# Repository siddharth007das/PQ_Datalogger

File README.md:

# PQ_Datalogger
This work presents a high-precision, edge-computing data logger for real-time spike-based load profiling. The system integrates Halleffect current sensors, high-voltage transducers, and high-speed ADCs controlled by an STM32H7 microcontroller to perform synchronised voltage–current sampling, PQ computation, and transient detection.

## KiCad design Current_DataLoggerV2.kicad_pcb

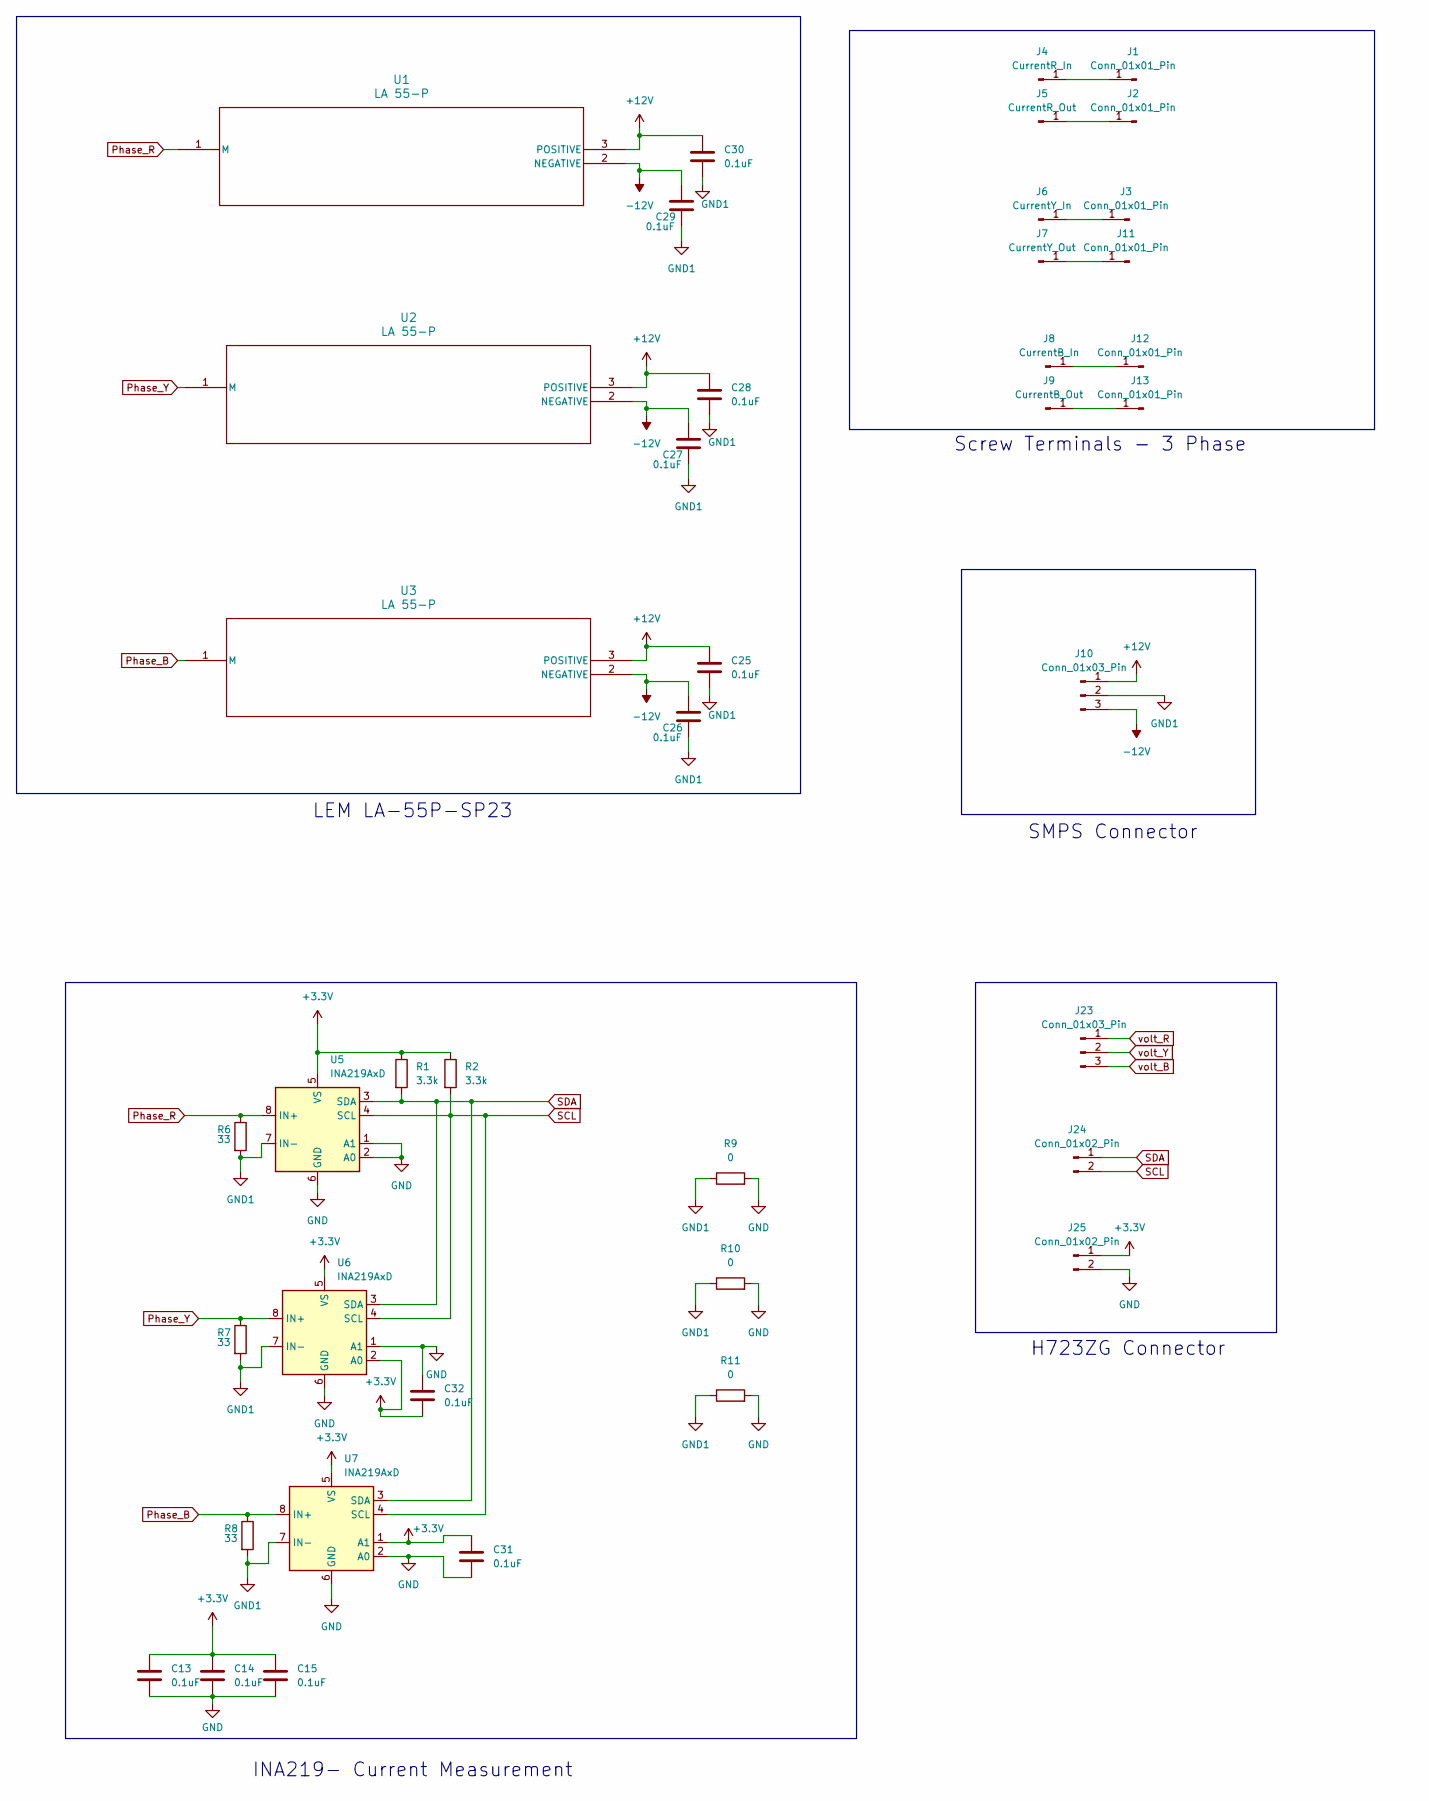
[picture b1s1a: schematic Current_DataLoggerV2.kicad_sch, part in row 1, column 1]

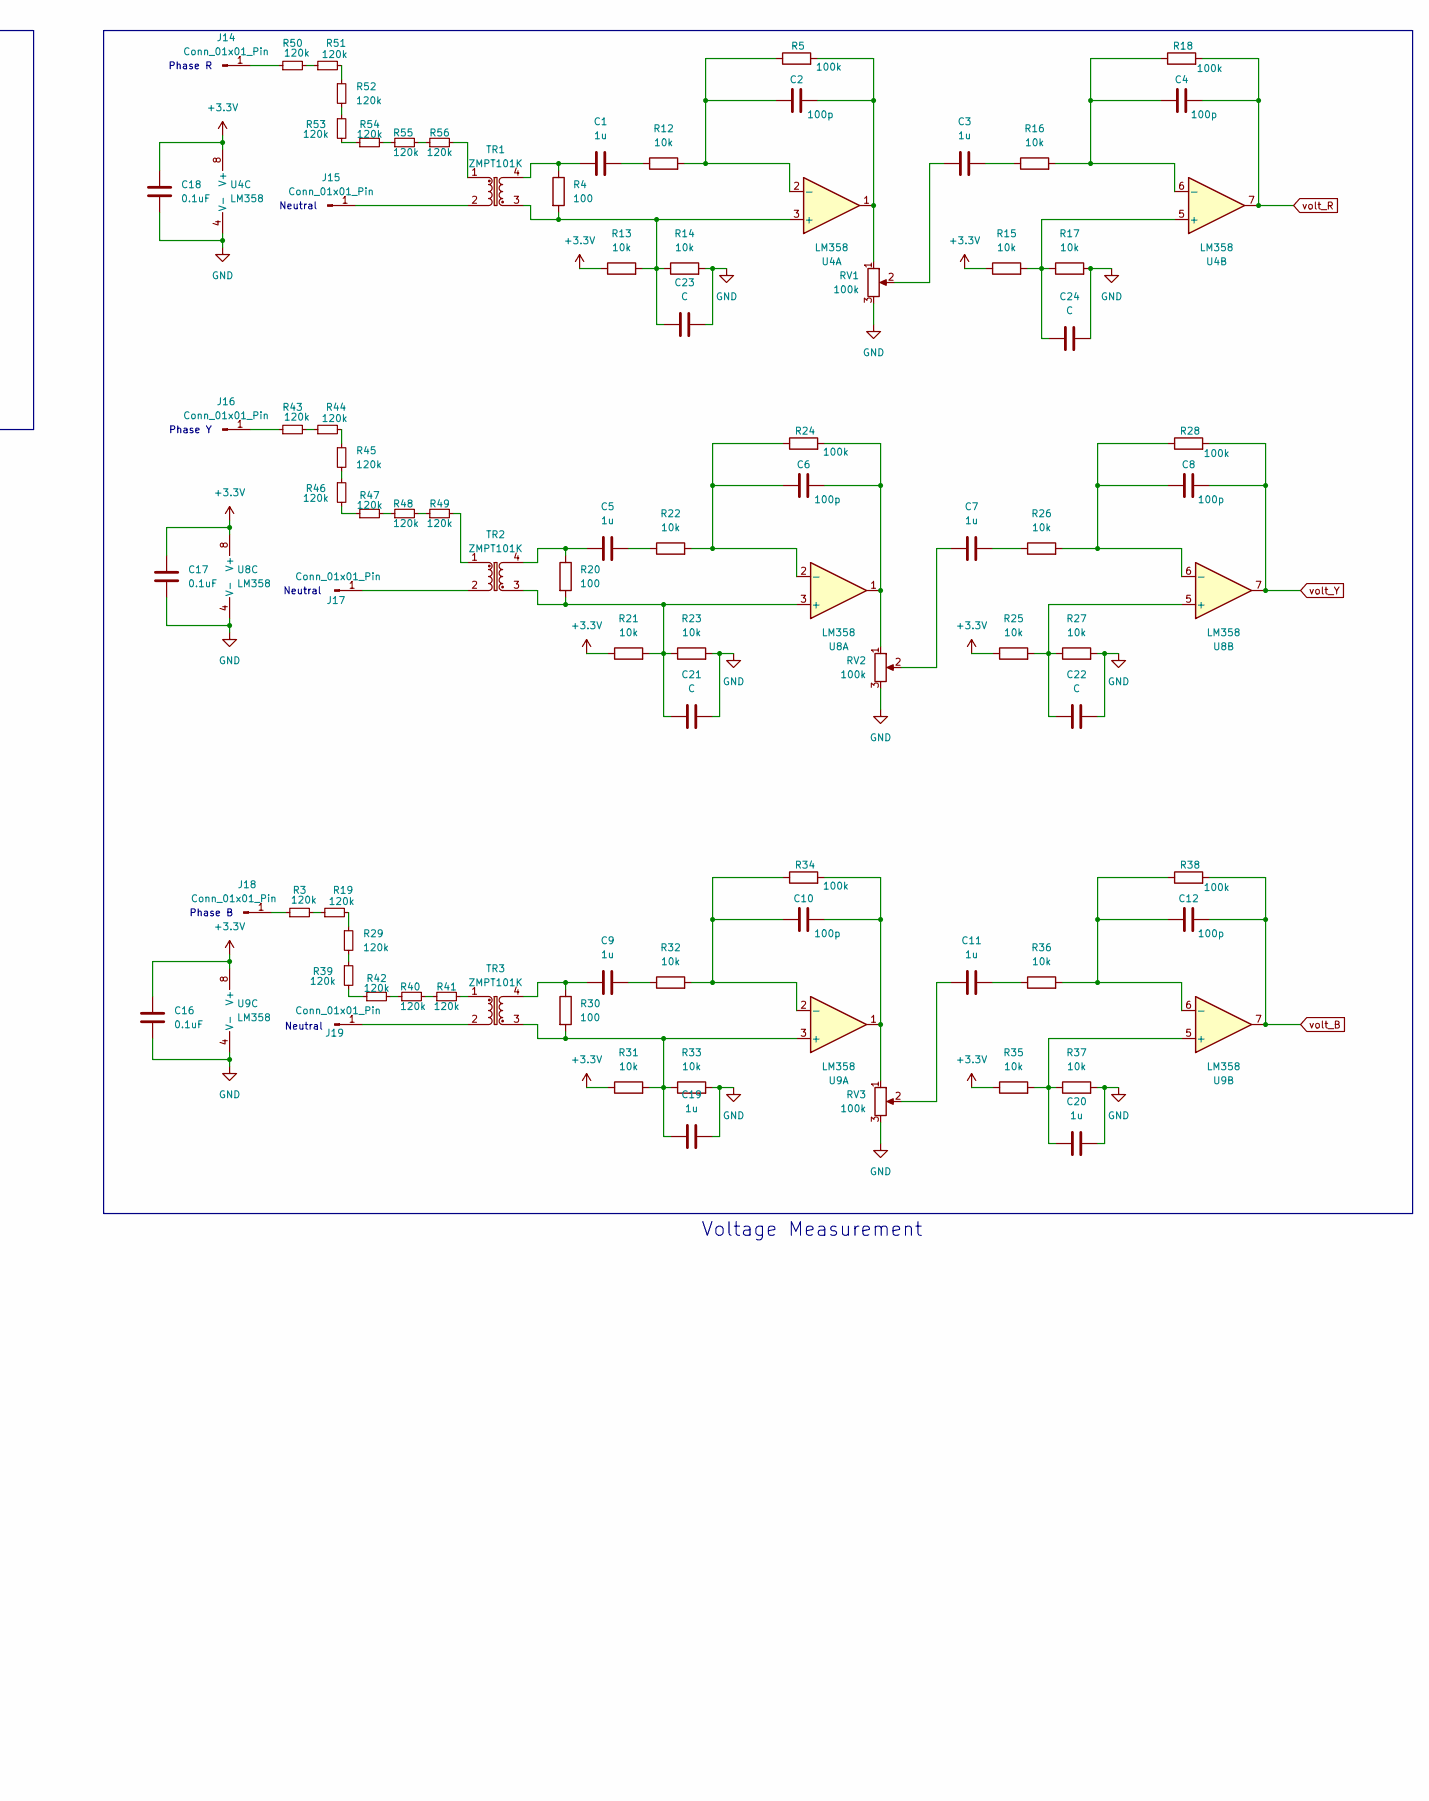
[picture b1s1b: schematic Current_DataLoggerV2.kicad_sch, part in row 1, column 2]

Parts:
C1, C3, C5, C7, C9, C11, C19, C20: 1u; C_1206_3216Metric_Pad1.33x1.80mm_HandSolder
C2, C4, C6, C8, C10, C12: 100p; C_1206_3216Metric_Pad1.33x1.80mm_HandSolder
C13, C14, C15, C16, C17, C18, C25, C26, C27, C28, C29, C30, C31, C32: 0.1uF; C_1206_3216Metric_Pad1.33x1.80mm_HandSolder
C21, C22, C23, C24: C; C_1206_3216Metric_Pad1.33x1.80mm_HandSolder
J1, J2, J3, J11, J12, J13, J14, J15, J16, J17, J18, J19: Conn_01x01_Pin; Banana_Jack_4mm
J4: CurrentR_In; Banana_Jack_4mm
J5: CurrentR_Out; Banana_Jack_4mm
J6: CurrentY_In; Banana_Jack_4mm
J7: CurrentY_Out; Banana_Jack_4mm
J8: CurrentB_In; Banana_Jack_4mm
J9: CurrentB_Out; Banana_Jack_4mm
J10, J23: Conn_01x03_Pin; JST_EH_B3B-EH-A_1x03_P2.50mm_Vertical
J24, J25: Conn_01x02_Pin; JST_EH_B2B-EH-A_1x02_P2.50mm_Vertical
R1, R2: 3.3k; R_1206_3216Metric_Pad1.30x1.75mm_HandSolder
R3, R19, R29, R39, R40, R41, R42, R43, R44, R45, R46, R47, R48, R49, R50, R51, R52, R53, R54, R55, R56: 120k; R_1206_3216Metric_Pad1.30x1.75mm_HandSolder
R4, R20, R30: 100; R_1206_3216Metric_Pad1.30x1.75mm_HandSolder
R5, R18, R24, R28, R34, R38: 100k; R_1206_3216Metric_Pad1.30x1.75mm_HandSolder
R6, R7, R8: 33; R_1206_3216Metric_Pad1.30x1.75mm_HandSolder
R9, R10, R11: 0; R_1206_3216Metric_Pad1.30x1.75mm_HandSolder
R12, R13, R14, R15, R16, R17, R21, R22, R23, R25, R26, R27, R31, R32, R33, R35, R36, R37: 10k; R_1206_3216Metric_Pad1.30x1.75mm_HandSolder
RV1, RV2, RV3: 100k; Potentiometer_Bourns_3296W_Vertical
TR1, TR2, TR3: ZMPT101K; Transformer_Zeming_ZMPT101K
U1, U2, U3: LA 55-P; LA 55-P_LEM
U4, U8, U9: LM358; SOIC-8_3.9x4.9mm_P1.27mm
U5, U6, U7: INA219AxD; SOIC-8_3.9x4.9mm_P1.27mm

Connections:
+3.3V: C13.1, C14.1, C15.1, C16.1, C17.1, C18.1, C31.1, C32.2, J25.1, R1.1, R2.1, R13.1, R15.1, R21.1, R25.1, R31.1, R35.1, U4.8 (V+), U5.5 (VS), U6.2 (A0), U6.5 (VS), U7.1 (A1), U7.5 (VS), U8.8 (V+), U9.8 (V+)
+12V: C25.1, C28.1, C30.1, J10.1, U1.3 (POSITIVE), U2.3 (POSITIVE), U3.3 (POSITIVE)
-12V: C26.1, C27.1, C29.1, J10.3, U1.2 (NEGATIVE), U2.2 (NEGATIVE), U3.2 (NEGATIVE)
GND: C13.2, C14.2, C15.2, C16.2, C17.2, C18.2, C19.2, C20.2, C21.2, C22.2, C23.2, C24.2, C31.2, C32.1, J25.2, R9.2, R10.2, R11.2, R14.2, R17.2, R23.2, R27.2, R33.2, R37.2, RV1.3, RV2.3, RV3.3, U4.4 (V-), U5.1 (A1), U5.2 (A0), U5.6 (GND), U6.1 (A1), U6.6 (GND), U7.2 (A0), U7.6 (GND), U8.4 (V-), U9.4 (V-)
GND1: C25.2, C26.2, C27.2, C28.2, C29.2, C30.2, J10.2, R6.2, R7.2, R8.2, R9.1, R10.1, R11.1, U5.7 (IN-), U6.7 (IN-), U7.7 (IN-)
unnamed: C1.1, R4.1, TR1.4
unnamed: C1.2, R12.1
unnamed: C2.2, R5.2, RV1.1, U4.1
unnamed: C3.1, RV1.2
unnamed: C3.2, R16.1
unnamed: C5.1, R20.1, TR2.4
unnamed: C5.2, R22.1
unnamed: C6.2, R24.2, RV2.1, U8.1
unnamed: C7.1, RV2.2
unnamed: C7.2, R26.1
unnamed: C9.1, R30.1, TR3.4
unnamed: C9.2, R32.1
unnamed: C10.2, R34.2, RV3.1, U9.1
unnamed: C11.1, RV3.2
unnamed: C11.2, R36.1
unnamed: J1.1, J4.1
unnamed: J2.1, J5.1
unnamed: J3.1, J6.1
unnamed: J7.1, J11.1
unnamed: J8.1, J12.1
unnamed: J9.1, J13.1
unnamed: J14.1, R50.1
unnamed: J15.1, TR1.2
unnamed: J16.1, R43.1
unnamed: J17.1, TR2.2
unnamed: J18.1, R3.1
unnamed: J19.1, TR3.2
unnamed: R3.2, R19.1
unnamed: R19.2, R29.1
unnamed: R29.2, R39.1
unnamed: R39.2, R42.1
unnamed: R40.1, R42.2
unnamed: R40.2, R41.1
unnamed: R41.2, TR3.1
unnamed: R43.2, R44.1
unnamed: R44.2, R45.1
unnamed: R45.2, R46.1
unnamed: R46.2, R47.1
unnamed: R47.2, R48.1
unnamed: R48.2, R49.1
unnamed: R49.2, TR2.1
unnamed: R50.2, R51.1
unnamed: R51.2, R52.1
unnamed: R52.2, R53.1
unnamed: R53.2, R54.1
unnamed: R54.2, R55.1
unnamed: R55.2, R56.1
unnamed: R56.2, TR1.1
unnamed: C23.1, R4.2, R13.2, R14.1, TR1.3, U4.3 (+)
unnamed: C2.1, R5.1, R12.2, U4.2 (-)
unnamed: C24.1, R15.2, R17.1, U4.5 (+)
unnamed: C4.1, R16.2, R18.1, U4.6 (-)
unnamed: C21.1, R20.2, R21.2, R23.1, TR2.3, U8.3 (+)
unnamed: C6.1, R22.2, R24.1, U8.2 (-)
unnamed: C22.1, R25.2, R27.1, U8.5 (+)
unnamed: C8.1, R26.2, R28.1, U8.6 (-)
unnamed: C19.1, R30.2, R31.2, R33.1, TR3.3, U9.3 (+)
unnamed: C10.1, R32.2, R34.1, U9.2 (-)
unnamed: C20.1, R35.2, R37.1, U9.5 (+)
unnamed: C12.1, R36.2, R38.1, U9.6 (-)
Phase_B: R8.1, U3.1 (M), U7.8 (IN+)
Phase_R: R6.1, U1.1 (M), U5.8 (IN+)
Phase_Y: R7.1, U2.1 (M), U6.8 (IN+)
SCL: J24.2, R2.2, U5.4 (SCL), U6.4 (SCL), U7.4 (SCL)
SDA: J24.1, R1.2, U5.3 (SDA), U6.3 (SDA), U7.3 (SDA)
volt_B: C12.2, J23.3, R38.2, U9.7
volt_R: C4.2, J23.1, R18.2, U4.7
volt_Y: C8.2, J23.2, R28.2, U8.7

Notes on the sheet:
Screw Terminals - 3 Phase
Phase R
Neutral
SMPS Connector
Phase B
Phase Y
H723ZG Connector
INA219- Current Measurement
LEM LA-55P-SP23
Voltage Measurement

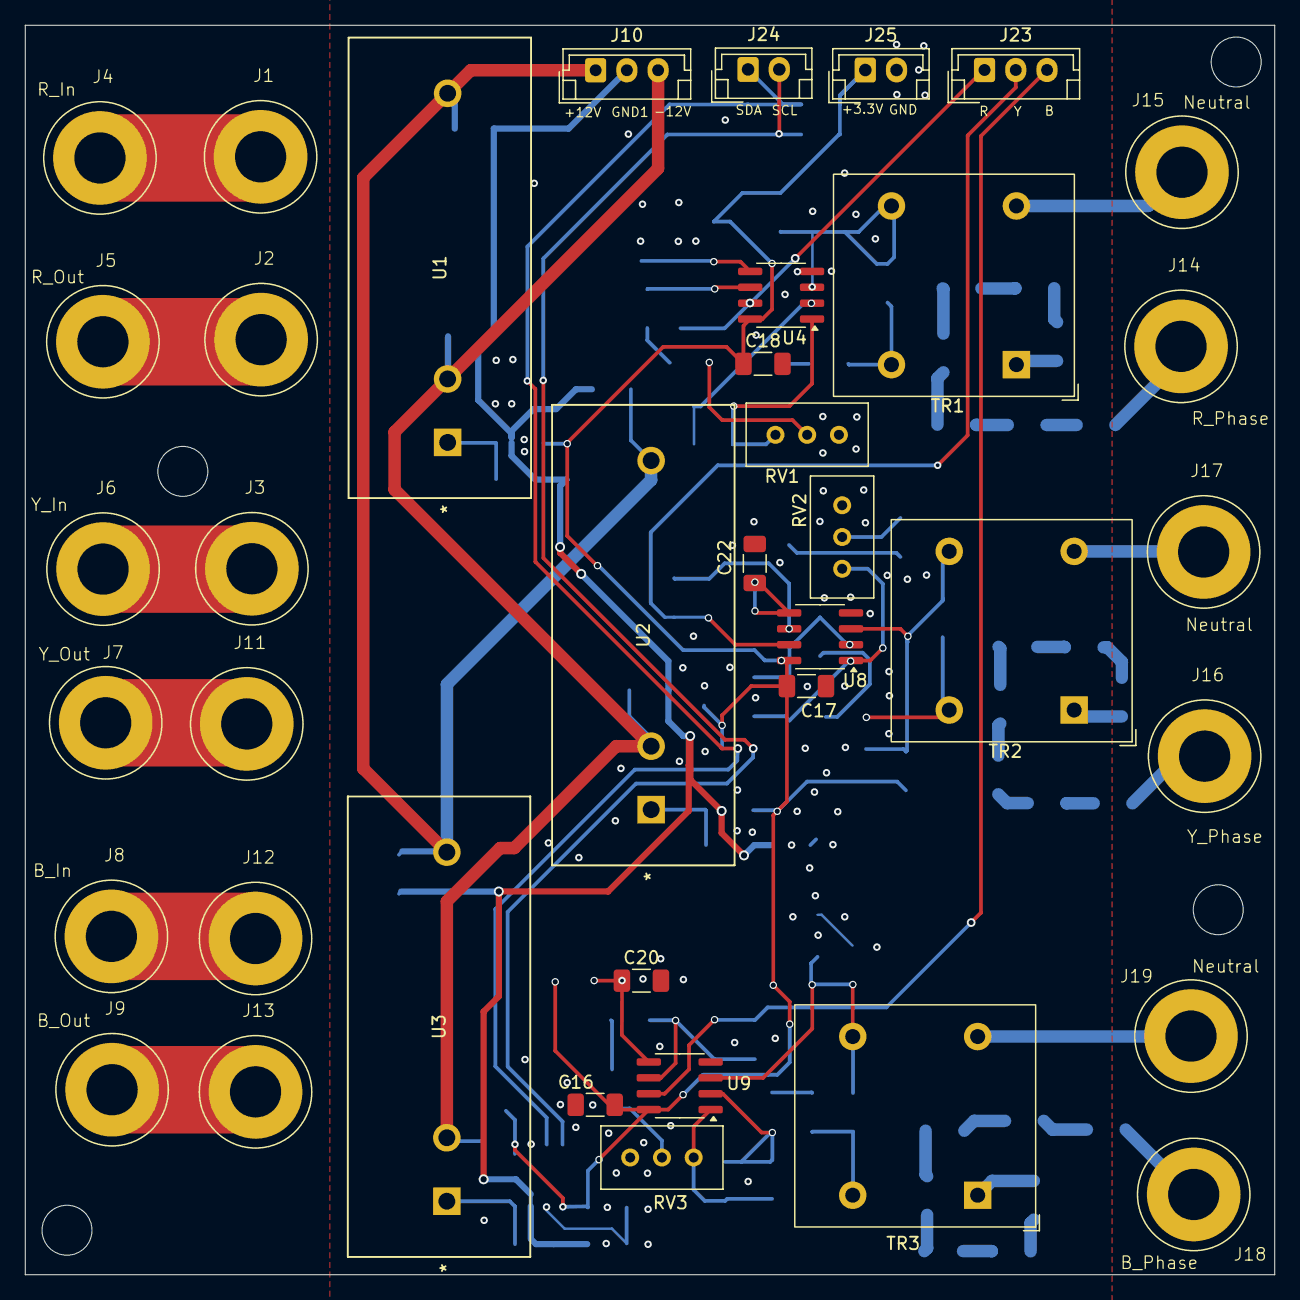
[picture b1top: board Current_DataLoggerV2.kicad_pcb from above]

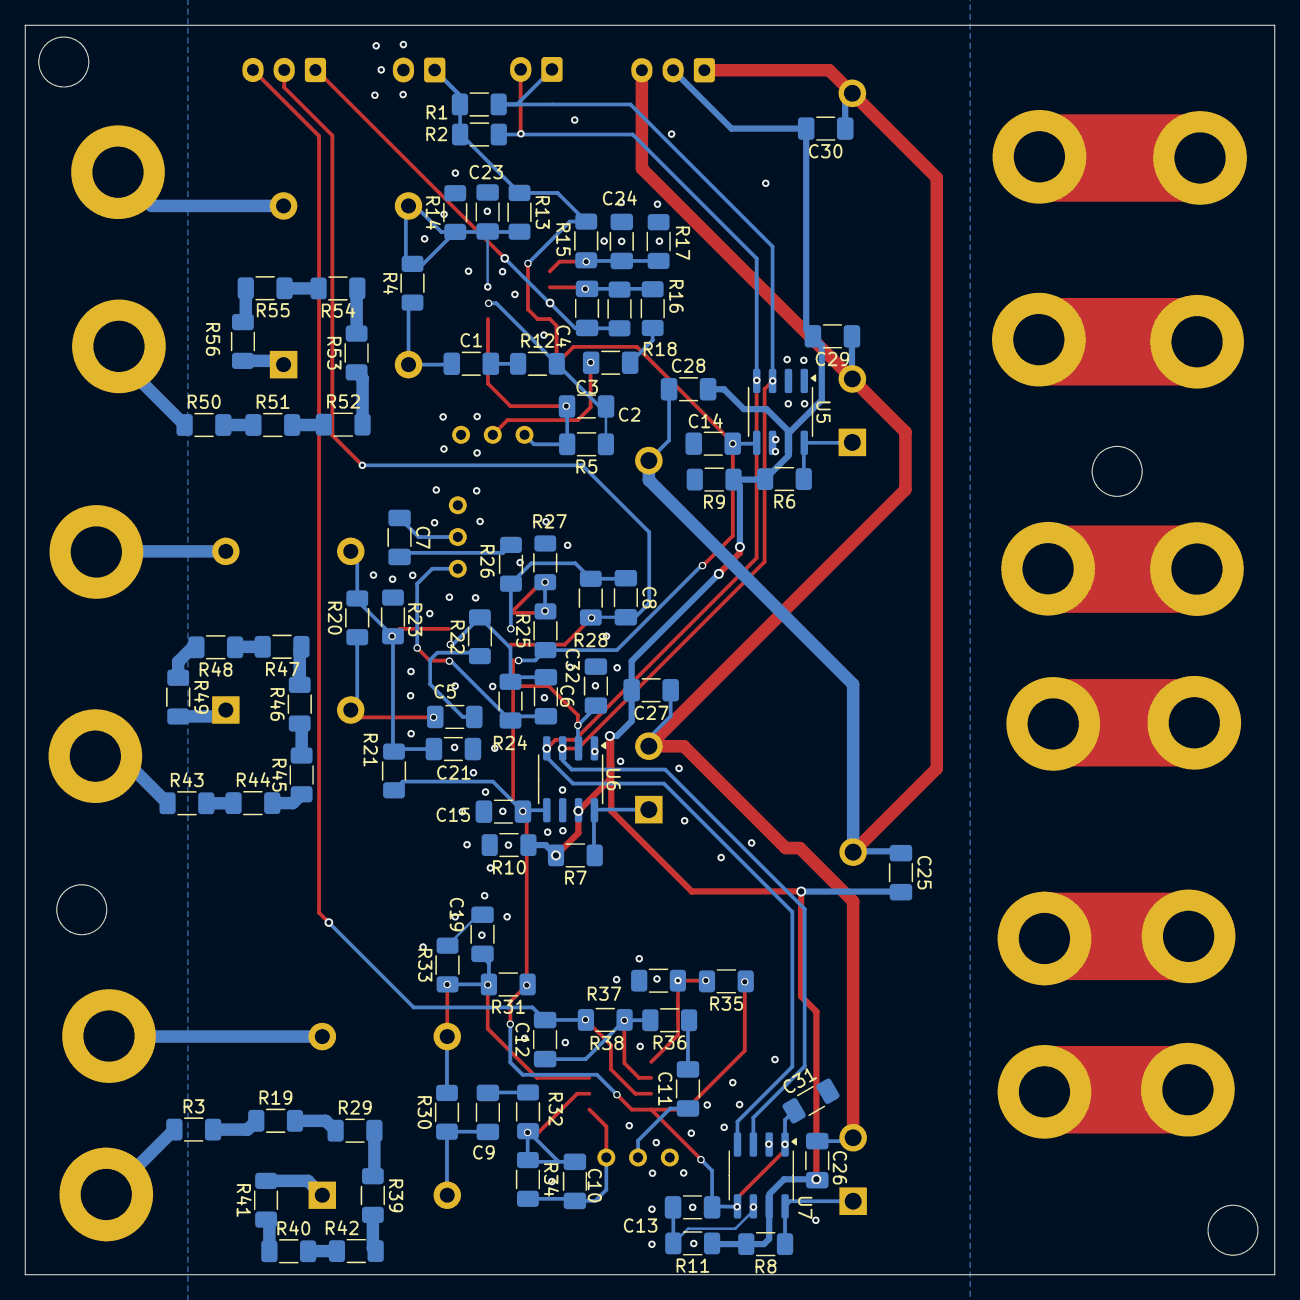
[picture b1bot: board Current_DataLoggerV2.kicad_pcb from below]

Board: 2 copper layers, 100.0 x 100.0 mm, 125 parts (86 on the bottom side), 73 nets.
